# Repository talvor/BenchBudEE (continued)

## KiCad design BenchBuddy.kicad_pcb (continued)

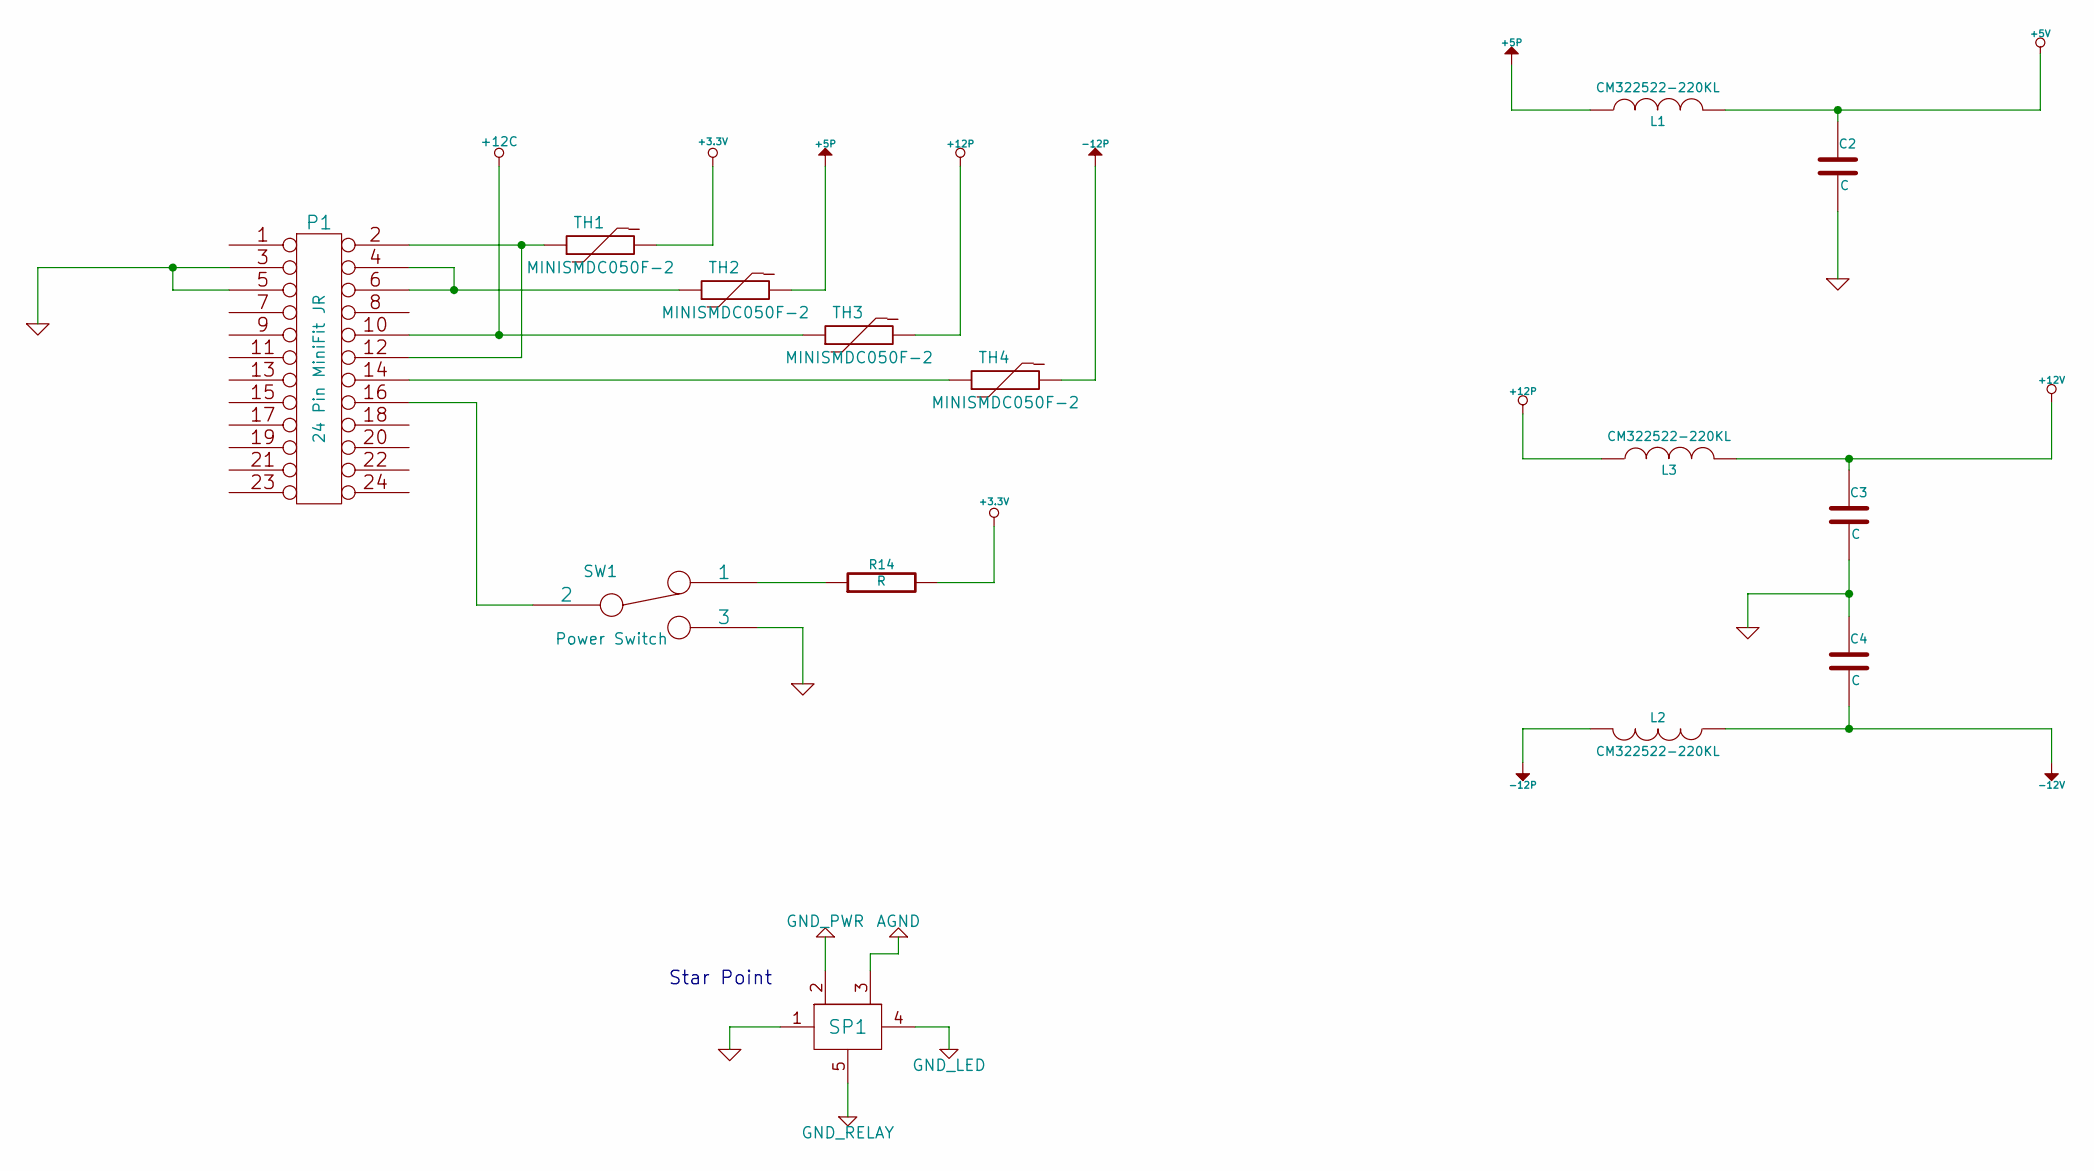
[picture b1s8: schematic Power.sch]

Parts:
C2, C3, C4: C
L1, L2, L3: CM322522-220KL; MFG Part Number CM322522-220KL
P1: 24 Pin MiniFit JR; MFG Part Number 39-30-1240
R14: R
SP1: PWR_STAR_POINT
SW1: Power Switch; MFG Part Number OS102011MA1QN1
TH1, TH2, TH3, TH4: MINISMDC050F-2; MFG Part Number MINISMDC050F-2

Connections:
+3.3V: R14.2, TH1.2; also elsewhere on the board
+5P: L1.1, TH2.2; also elsewhere on the board
+12C: P1.10, TH3.1; also elsewhere on the board
+12P: L3.1, TH3.2; also elsewhere on the board
+12V: C3.1, L3.2; also elsewhere on the board
-12P: L2.2, TH4.2
-12V: C4.2, L2.1; also elsewhere on the board
GND: C2.2, C3.2, C4.1, P1.3, P1.5, SP1.1, SW1.3; also elsewhere on the board
unnamed: P1.4, P1.6, TH2.1
unnamed: P1.2, P1.12, TH1.1
unnamed: P1.14, TH4.1
unnamed: P1.16, SW1.2
unnamed: R14.1, SW1.1

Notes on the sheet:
Star Point

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
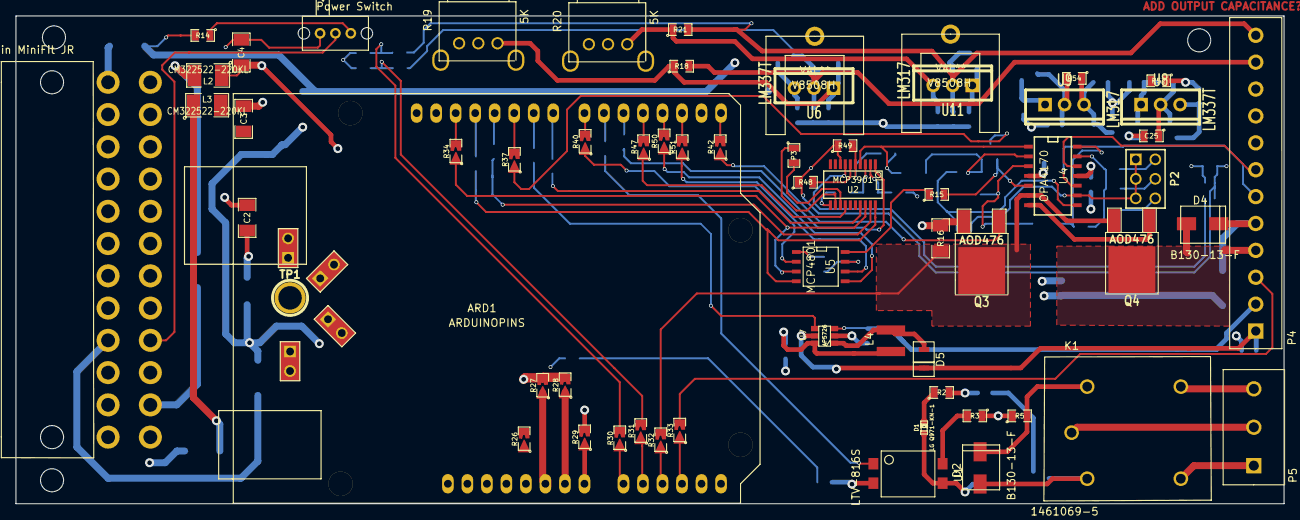
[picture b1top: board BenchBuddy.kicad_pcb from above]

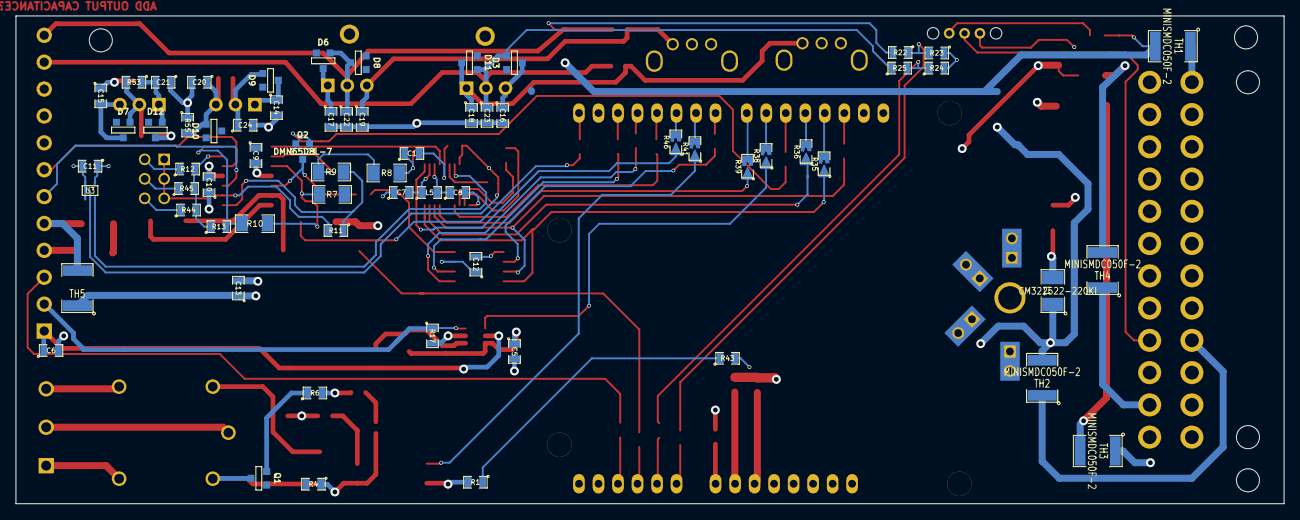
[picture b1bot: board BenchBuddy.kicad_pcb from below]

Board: 4 copper layers, 165.1 x 63.5 mm, 134 parts (65 on the bottom side), 102 nets.

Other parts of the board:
3 mm, 3 mm#2, 3 mm#3: VAL**; 3mm-NPTH
JP1, JP2, JP3, JP4: JUMPER; GND_POINT
L5: INDUCTOR; SM0805
TP1: CONN_1; 1pin
V8508H, V8508H#2: VAL**; V8508H

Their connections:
AGND: JP1.2; also elsewhere on the board
GND: JP1.1, JP2.1, JP3.1, JP4.1, TP1.1; also elsewhere on the board
GND_LED: JP3.2; also elsewhere on the board
GND_PWR: JP2.2; also elsewhere on the board
GND_RELAY: JP4.2; also elsewhere on the board

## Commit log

2014-01-30 Creation of initial blank files
2014-01-30 Creating a Schematic Skeleton
    Added a hierarchical page for Arduino, Power, Fan, LED_Driver, Relay,
    Terminal_Block and Thermocouple.
2014-01-30 Defining Your Inputs and Outputs
2014-02-04 Understanding the Thermocouple Module
2014-02-04 Understanding the Current/Fan Driver Module
2014-02-05 Understanding the Relay Module
2014-02-05 Understanding the Power Protection And Filtering Module
2014-02-06 Understanding the Power Control, Conditioning and Monitoring Module
2014-02-06 Understanding the Power Control, Conditioning and Monitoring Module - Part 2
2014-02-07 Understanding the LED Driver Module
2014-02-07 Understanding the Arduino Module
2014-02-10 Revisting the Current/Fan Module
2014-02-17 Intro to The Layout
    Setup PCBNew defaults
2014-02-18 Added BOM
2014-02-19 Associating and Placing the Relay Module
2014-02-19 Associating and Placing the Thermocouple Module
2014-02-20 Associating and Placing the Terminal/ATX Blocks
2014-02-22 Associating and Placing the Arduino Module
2014-02-24 Associating and Placing the Current/Fan Driver Module
2014-02-25 Associating and Placing the Power Protection and Filtering Module
2014-03-01 Layout Work Session 2
2014-03-01 Layout Work Session 3
2014-03-03 Layout Work Session 4
2014-03-03 Layout Work Session 6
2014-03-04 Layout Work Session 6
    Pulled from CE
2014-03-04 Layout Work Session 7
    Pulled from CE
2014-03-06 Layout Work Session 8
2014-03-06 Layout Work Session 9
2014-03-06 Layout Work Session 10
2014-03-07 Layout Work Session 12
    Pulled from CE.
    Session 11 missed due to corrupted pcb file pulled from CE
2014-03-10 Layout Work Session 14
    Pulled from CE
2014-03-10 Layout Work Session 15
    Pulled from CE
2014-03-11 Layout Work Session 16
    Pulled from CE
2014-03-11 Layout Work Session 17
    Pulled from CE
2014-03-12 Layout Work Session 18
    Pulled from CE
2014-03-13 Analog IO Cleanup/Additions
    Pulled from CE
